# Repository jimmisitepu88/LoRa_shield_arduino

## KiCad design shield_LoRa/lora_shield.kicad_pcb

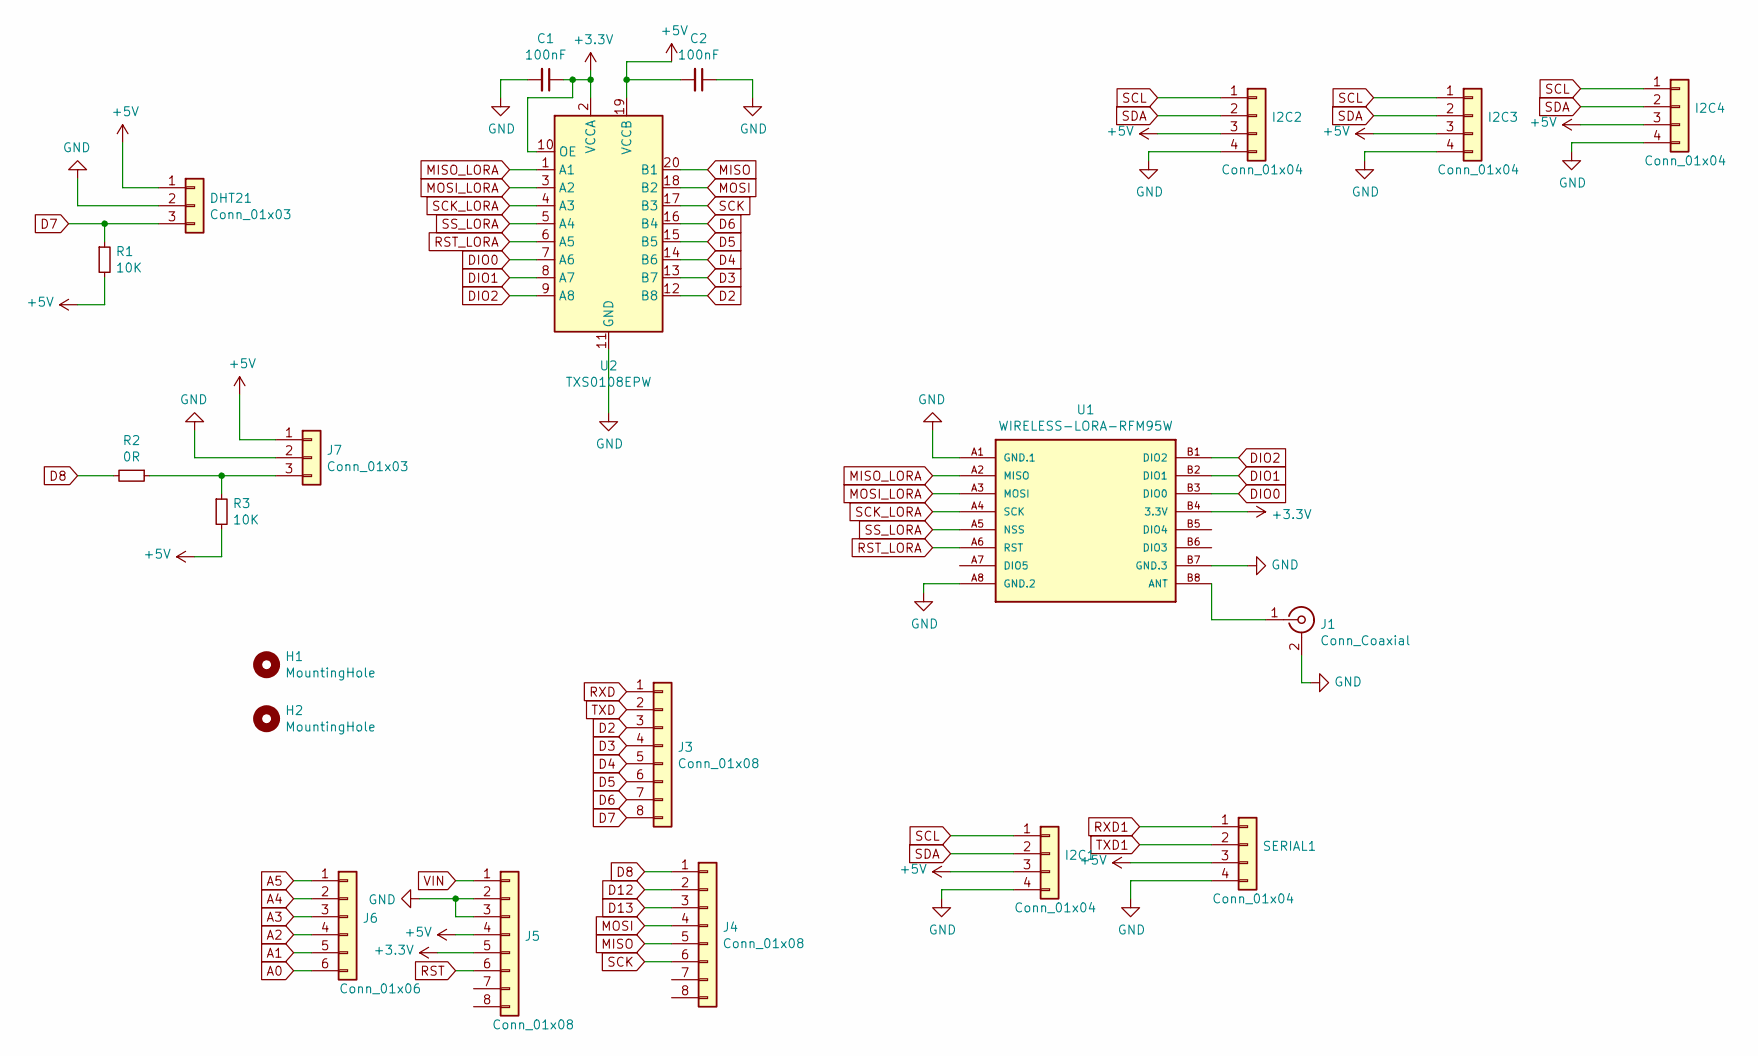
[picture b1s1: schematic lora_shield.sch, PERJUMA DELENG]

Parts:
C1, C2: 100nF; C_0603_1608Metric_Pad1.05x0.95mm_HandSolder
DHT21: Conn_01x03; PinHeader_1x03_P2.54mm_Vertical
H1, H2: MountingHole; MountingHole_3.2mm_M3
I2C1, I2C2, I2C3, I2C4: Conn_01x04; PinHeader_1x04_P2.54mm_Vertical
J1: Conn_Coaxial; SMA_Samtec_SMA-J-P-X-ST-EM1_EdgeMount
J3, J4, J5: Conn_01x08; PinSocket_1x08_P2.54mm_Vertical
J6: Conn_01x06; PinSocket_1x06_P2.54mm_Vertical
J7: Conn_01x03; PinHeader_1x03_P2.54mm_Vertical
R1, R3: 10K; R_0603_1608Metric_Pad1.05x0.95mm_HandSolder
R2: 0R; R_0603_1608Metric_Pad1.05x0.95mm_HandSolder
SERIAL1: Conn_01x04; PinHeader_1x04_P2.54mm_Vertical
U1: WIRELESS-LORA-RFM95W; WIRELESS-LORA-RFM95W#SMD
U2: TXS0108EPW; TSSOP-20_4.4x6.5mm_P0.65mm

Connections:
+3V3: C1.1, J5.5, U1.B4 (3.3V), U2.2 (VCCA), U2.10 (OE)
+5V: C2.2, DHT21.1, I2C1.3, I2C2.3, I2C3.3, I2C4.3, J5.4, J7.1, R1.2, R3.2, SERIAL1.3, U2.19 (VCCB)
A0: J6.6
A1: J6.5
A2: J6.4
A3: J6.3
A4: J6.2
A5: J6.1
D2: J3.3, U2.12 (B8)
D3: J3.4, U2.13 (B7)
D4: J3.5, U2.14 (B6)
D5: J3.6, U2.15 (B5)
D6: J3.7, U2.16 (B4)
D7: DHT21.3, J3.8, R1.1
D8: J4.1, R2.2
D12: J4.2
D13: J4.3
DIO0: U1.B3 (DIO0), U2.7 (A6)
DIO1: U1.B2 (DIO1), U2.8 (A7)
DIO2: U1.B1 (DIO2), U2.9 (A8)
GND: C1.2, C2.1, DHT21.2, I2C1.4, I2C2.4, I2C3.4, I2C4.4, J1.2 (Ext), J5.2, J5.3, J7.2, SERIAL1.4, U1.A1 (GND.1), U1.A8 (GND.2), U1.B7 (GND.3), U2.11 (GND)
MISO: J4.5, U2.20 (B1)
MISO_LORA: U1.A2 (MISO), U2.1 (A1)
MOSI: J4.4, U2.18 (B2)
MOSI_LORA: U1.A3 (MOSI), U2.3 (A2)
unnamed: J1.1 (In), U1.B8 (ANT)
unnamed: J7.3, R2.1, R3.1
RST: J5.6
RST_LORA: U1.A6 (RST), U2.6 (A5)
RXD: J3.1
RXD1: SERIAL1.1
SCK: J4.6, U2.17 (B3)
SCK_LORA: U1.A4 (SCK), U2.4 (A3)
SCL: I2C1.1, I2C2.1, I2C3.1, I2C4.1
SDA: I2C1.2, I2C2.2, I2C3.2, I2C4.2
SS_LORA: U1.A5 (NSS), U2.5 (A4)
TXD: J3.2
TXD1: SERIAL1.2
VIN: J5.1

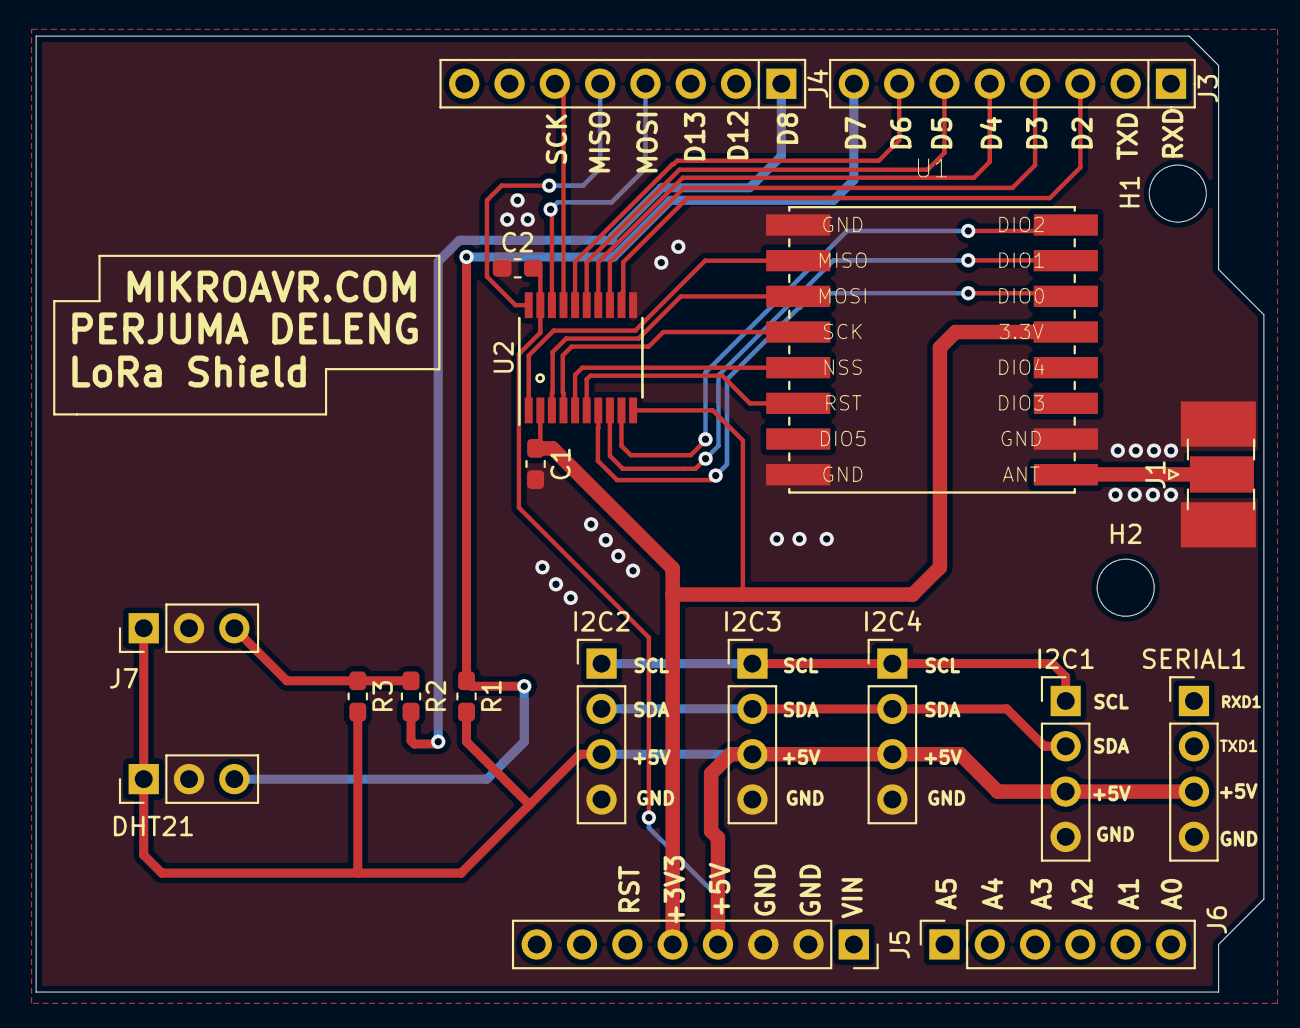
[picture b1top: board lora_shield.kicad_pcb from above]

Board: 2 copper layers, 68.8 x 53.6 mm, 21 parts (0 on the bottom side), 25 nets.
